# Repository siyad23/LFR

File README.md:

# Line Following Robot (LFR) with Rotary Encoder and OLED Display

This project is a Line Following Robot (LFR) system that uses a rotary encoder for menu navigation and an OLED display for user interaction. The system is built using an Arduino Nano and the Adafruit GFX library for the display.

## TODO

- Add double click feature
- Stop the counter from changing when it enters another menu
- Calibrate display calls a demo function
- Speed display changes a actual variable
- Add five more display item (exp:follow biasing turn or dmp, baising turn)
- Add the dmp editing menu

## Features

- **Rotary Encoder**: Navigate through the menu using a rotary encoder.
- **Switch Input**: A button is integrated with the rotary encoder for selection.
- **OLED Display**: Displays a menu with options and icons.
- **Menu System**: Includes options like "Calibrate," "Speed," and "DMP."
- **Debounce Logic**: Ensures stable input from the rotary encoder and switch.

## Components Used

- Arduino Nano
- Rotary Encoder
- OLED Display (SH1106)
- Push Button (integrated with the rotary encoder)

## File Structure

- **`main.cpp`**: The main entry point of the program.
- **`init.h`**: Handles basic initialization of the system.
- **`switch.h`**: Manages the rotary encoder and switch input.
- **`logo.h`**: Contains bitmap data for menu icons.
- **`display.h`**: Handles the OLED display and menu rendering.
- **`platformio.ini`**: PlatformIO configuration file.

## Installation

1. Clone this repository to your local machine.
2. Open the project in [PlatformIO](https://platformio.org/).
3. Ensure the required libraries are installed:
   - [Adafruit GFX Library](https://github.com/adafruit/Adafruit-GFX-Library)
4. Connect the hardware components as described in the **Wiring** section.
5. Upload the code to your Arduino Nano.

## Wiring

| Component          | Arduino Pin |
| ------------------ | ----------- |
| Rotary Encoder CLK | D4          |
| Rotary Encoder DT  | D5          |
| Rotary Encoder SW  | D6          |
| OLED Display SDA   | A4          |
| OLED Display SCL   | A5          |

## Usage

1. Power on the system.
2. Use the rotary encoder to navigate through the menu.
3. Press the button on the rotary encoder to select an option.
4. The OLED display will update based on the selected menu item.

## Menu Options

1. **Calibrate**: Displays the calibration icon and text.
2. **Speed**: Displays the speed icon and text.
3. **DMP**: Displays the DMP icon and text.

## Code Overview

### `main.cpp`

- Initializes the system using `basic_init()`, `switch_init()`, and `display_init()`.
- Handles the rotary encoder input and updates the menu display.

### `switch.h`

- Manages the rotary encoder and switch input.
- Includes debounce logic for stable input handling.

### `display.h`

- Renders the menu on the OLED display.
- Uses the Adafruit GFX library for drawing text and icons.

### `logo.h`

- Contains bitmap data for the menu icons.

### `platformio.ini`

- Configures the PlatformIO environment for the Arduino Nano.
- Specifies the required libraries and build flags.

## Dependencies

- [Adafruit GFX Library](https://github.com/adafruit/Adafruit-GFX-Library)

## License

This project is licensed under the MIT License. See the `LICENSE` file for details.

## Acknowledgments

- [Adafruit](https://www.adafruit.com/) for their excellent libraries and hardware.
- [PlatformIO](https://platformio.org/) for providing a powerful development environment.

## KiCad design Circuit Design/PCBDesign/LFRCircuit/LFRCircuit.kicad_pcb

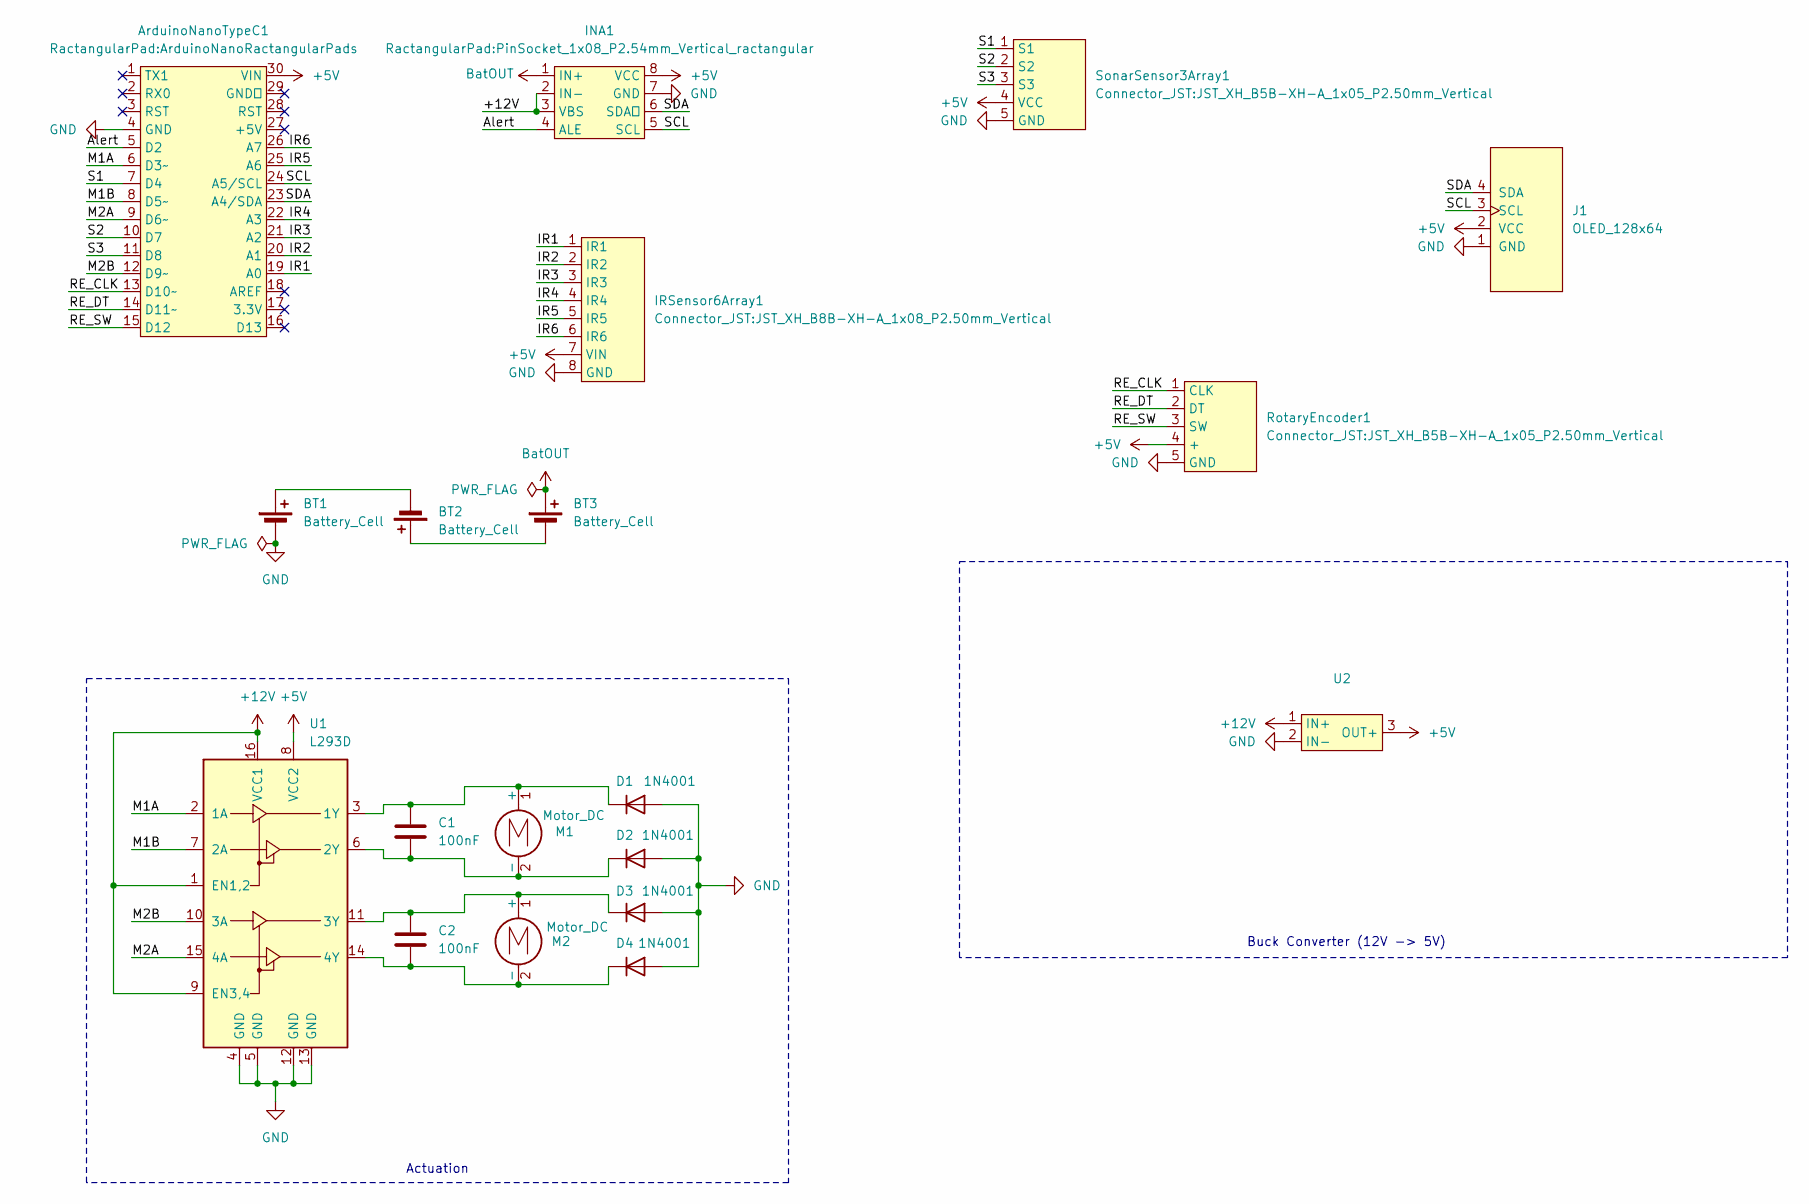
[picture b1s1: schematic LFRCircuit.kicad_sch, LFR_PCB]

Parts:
ArduinoNanoTypeC1: ArduinoNanoRactangularPads
BT1, BT2, BT3: Battery_Cell; JST_XH_B2B-XH-A_1x02_P2.50mm_Vertical_ractangular
C1, C2: 100nF; C_Disc_D5.0mm_W2.5mm_P5.00mm
D1, D2, D3, D4: 1N4001; D_DO-41_SOD81_P7.62mm_Horizontal
INA1: PinSocket_1x08_P2.54mm_Vertical_ractangular
IRSensor6Array1: JST_XH_B8B-XH-A_1x08_P2.50mm_Vertical
J1: OLED_128x64
M1, M2: Motor_DC; JST_XH_B2B-XH-A_1x02_P2.50mm_Vertical_ractangular
RotaryEncoder1: JST_XH_B5B-XH-A_1x05_P2.50mm_Vertical
SonarSensor3Array1: JST_XH_B5B-XH-A_1x05_P2.50mm_Vertical
U1: L293D; DIP-16_W7.62mm_ractangularPads
U2: JST_XH_B3B-XH-A_1x03_P2.50mm_Vertical

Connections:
+5V: ArduinoNanoTypeC1.30 (VIN), INA1.8 (VCC), IRSensor6Array1.7 (VIN), J1.2 (VCC), RotaryEncoder1.4 (+), SonarSensor3Array1.4 (VCC), U1.8 (VCC2), U2.3 (OUT+)
+12V: INA1.2 (IN-), INA1.3 (VBS), U1.1 (EN1,2), U1.9 (EN3,4), U1.16 (VCC1), U2.1 (IN+)
/Alert: ArduinoNanoTypeC1.5 (D2), INA1.4 (ALE)
/IR1: ArduinoNanoTypeC1.19 (A0), IRSensor6Array1.1 (IR1)
/IR2: ArduinoNanoTypeC1.20 (A1), IRSensor6Array1.2 (IR2)
/IR3: ArduinoNanoTypeC1.21 (A2), IRSensor6Array1.3 (IR3)
/IR4: ArduinoNanoTypeC1.22 (A3), IRSensor6Array1.4 (IR4)
/IR5: ArduinoNanoTypeC1.25 (A6), IRSensor6Array1.5 (IR5)
/IR6: ArduinoNanoTypeC1.26 (A7), IRSensor6Array1.6 (IR6)
/M1A: ArduinoNanoTypeC1.6 (D3~), U1.2 (1A)
/M1B: ArduinoNanoTypeC1.8 (D5~), U1.7 (2A)
/M2A: ArduinoNanoTypeC1.9 (D6~), U1.15 (4A)
/M2B: ArduinoNanoTypeC1.12 (D9~), U1.10 (3A)
/RE_CLK: ArduinoNanoTypeC1.13 (D10~), RotaryEncoder1.1 (CLK)
/RE_DT: ArduinoNanoTypeC1.14 (D11~), RotaryEncoder1.2 (DT)
/RE_SW: ArduinoNanoTypeC1.15 (D12), RotaryEncoder1.3 (SW)
/S1: ArduinoNanoTypeC1.7 (D4), SonarSensor3Array1.1 (S1)
/S2: ArduinoNanoTypeC1.10 (D7), SonarSensor3Array1.2 (S2)
/S3: ArduinoNanoTypeC1.11 (D8), SonarSensor3Array1.3 (S3)
/SCL: ArduinoNanoTypeC1.24 (A5/SCL), INA1.5 (SCL), J1.3 (SCL)
/SDA: ArduinoNanoTypeC1.23 (A4/SDA), INA1.6 (SDA), J1.4 (SDA)
BatOUT: BT3.1 (+), INA1.1 (IN+)
GND: ArduinoNanoTypeC1.4 (GND), BT1.2 (-), D1.2 (A), D2.2 (A), D3.2 (A), D4.2 (A), INA1.7 (GND), IRSensor6Array1.8 (GND), J1.1 (GND), RotaryEncoder1.5 (GND), SonarSensor3Array1.5 (GND), U1.4 (GND), U1.5 (GND), U1.12 (GND), U1.13 (GND), U2.2 (IN-)
unnamed: BT1.1 (+), BT2.2 (-)
unnamed: BT2.1 (+), BT3.2 (-)
unnamed: C1.1, D1.1 (K), M1.1 (+), U1.3 (1Y)
unnamed: C1.2, D2.1 (K), M1.2 (-), U1.6 (2Y)
unnamed: C2.1, D3.1 (K), M2.1 (+), U1.11 (3Y)
unnamed: C2.2, D4.1 (K), M2.2 (-), U1.14 (4Y)

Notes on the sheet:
Actuation
Buck Converter (12V -> 5V)

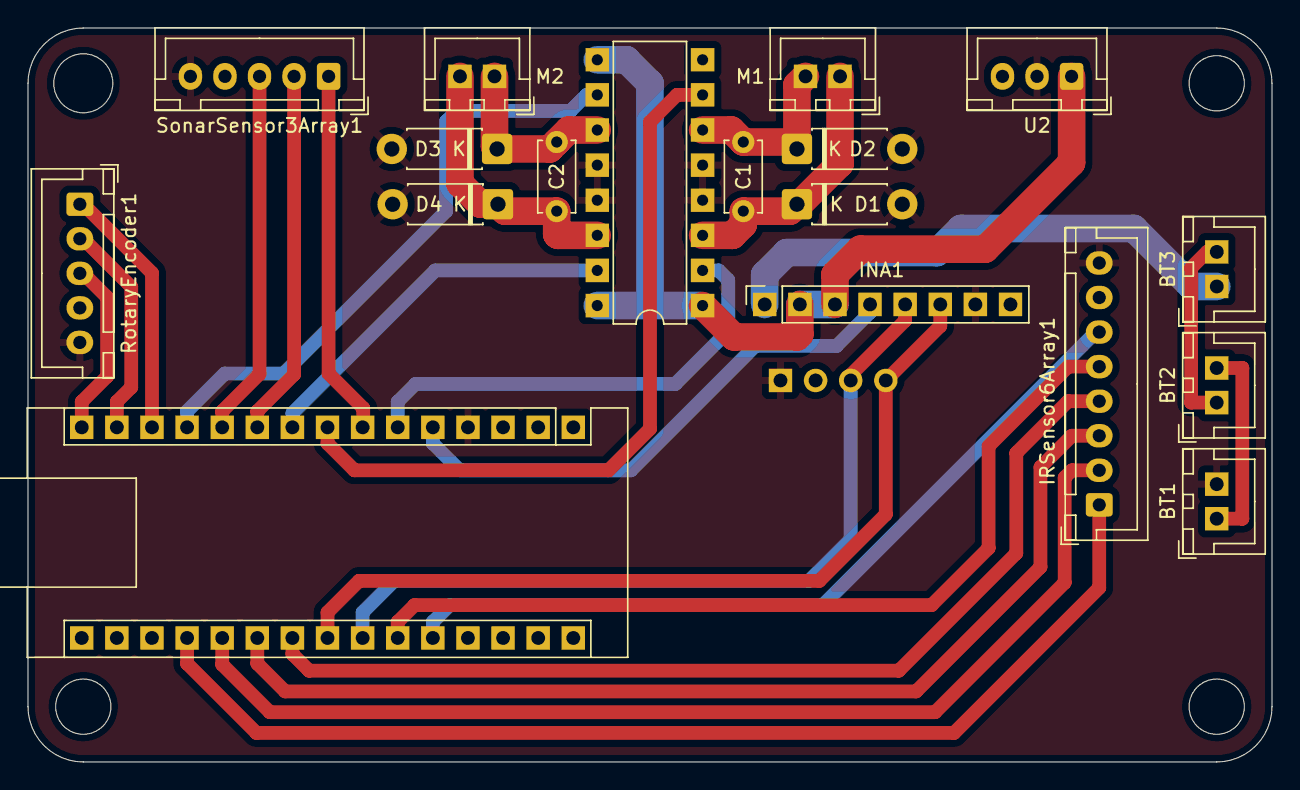
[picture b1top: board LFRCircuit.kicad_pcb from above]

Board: 2 copper layers, 90.0 x 53.1 mm, 19 parts (0 on the bottom side), 29 nets.

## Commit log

2025-03-24 Removed something
2025-04-06 added switch
2025-04-06 Display integration with switch
2025-04-13 Added menu Item
2025-04-13 Added Scalability Menu
2025-04-13 organised font file
2025-04-13 Optimized Compiling
2025-04-13 Added Readme file
2025-04-13 Create LICENSE
2025-04-13 Added Menu Level
2025-04-13 Added Calibrate Menu
2025-04-13 Added other menu screen
2025-04-13 Added TODO list to README File
2025-04-14 Edited README file
2025-05-03 Added Double and long press feature. Well deepSeek added. I am too lazy to understand.
2025-05-04 Fixed a lot
2025-05-05 Huge Change
2025-07-05 Something New
2025-07-05 Fixed
2025-07-05 Fixed2
2025-07-05 Fixed3
2025-07-05 PCB Schematic is partially Done
2025-07-05 Added Rotary Encoder and OLED Display Schematic
2025-07-07 Finalized the Schematics
2025-07-07 Placed on the PCB
2025-07-23 Circuit design is completed
2025-07-23 Tweaked a little bit
2025-07-26 Updated PCB
2025-07-26 Added chassis design files
2025-08-03 added design files and new code
